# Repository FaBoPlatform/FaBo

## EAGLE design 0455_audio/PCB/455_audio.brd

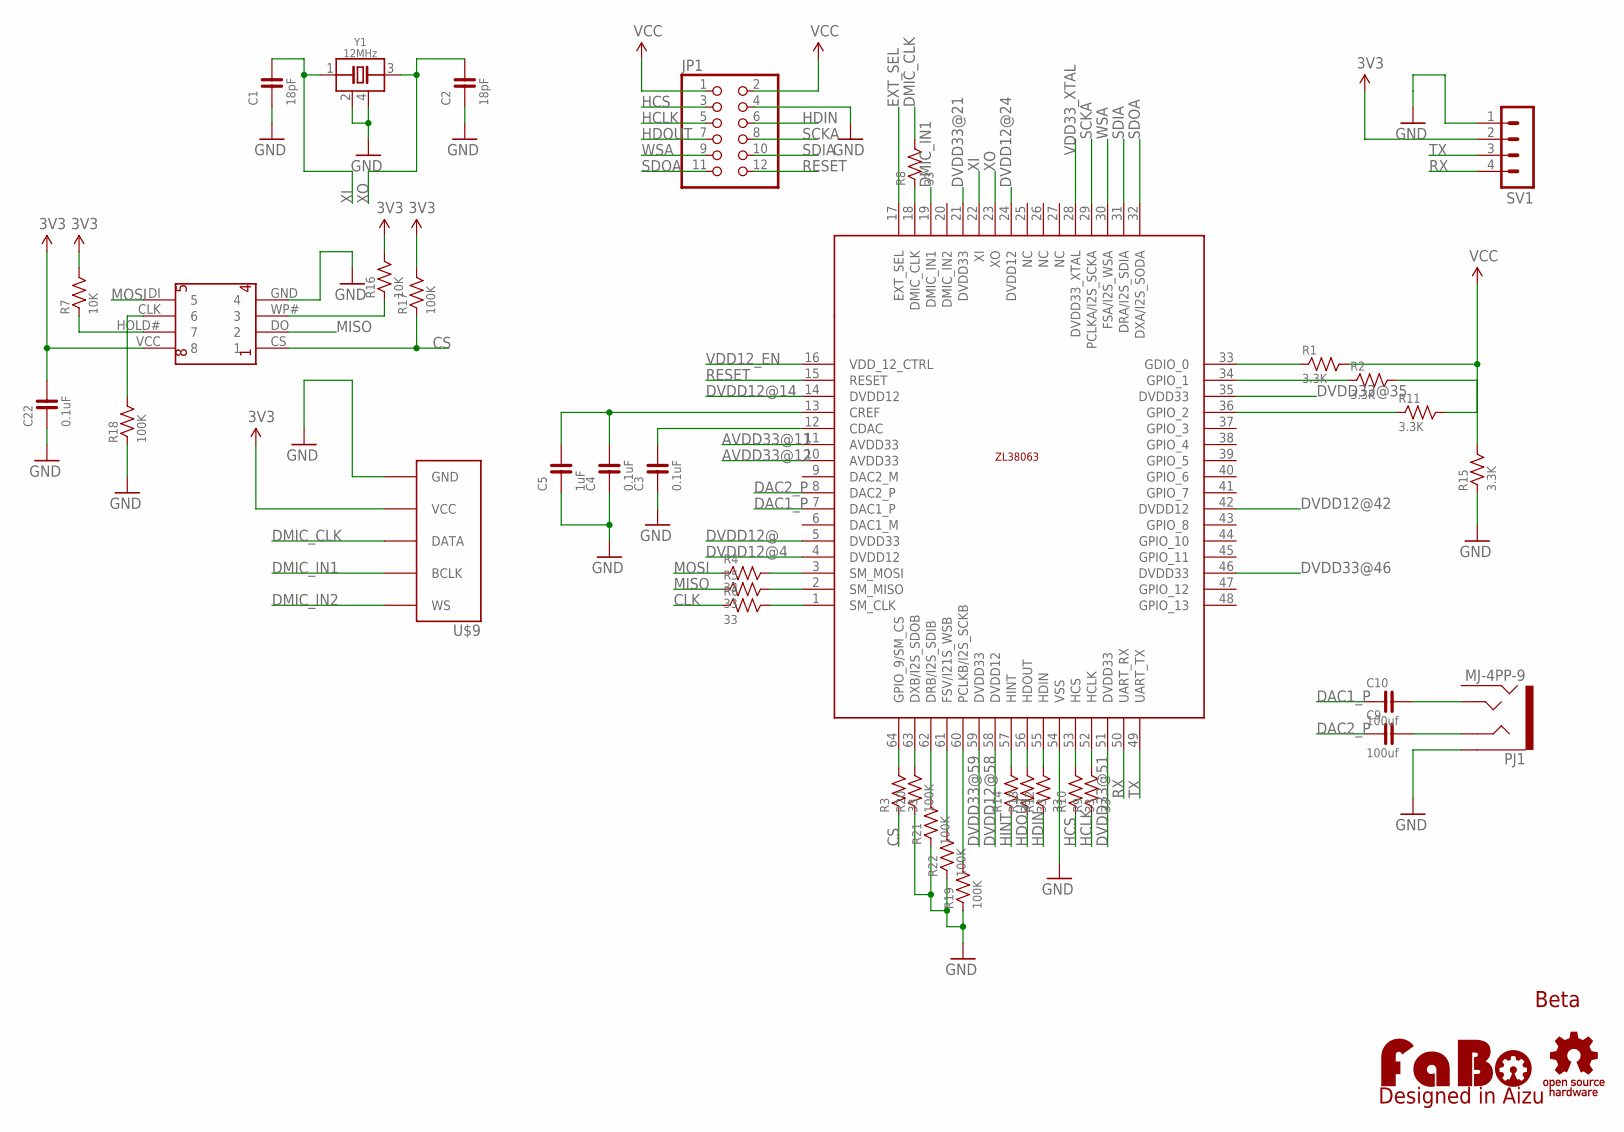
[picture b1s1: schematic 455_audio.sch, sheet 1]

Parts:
C1, C2: 18pF; 0603
C3, C4, C22: 0.1uF; 0603
C5: 1uF; 0603
C9, C10: 100uf; 0603
JP1: PINHD-2X6; 2X06
LOGO1: LOGO_FABO-M; LOGO_FABO_M
PJ1: MJ-4PP-9; PHONEJACK-MJ-4PP-9
R1, R2, R11, R15: 3.3K; 0603
R3, R4, R5, R6, R8, R9, R10, R12, R13, R14: 33; 0603
R7, R16: 10K; 0603
R17, R18, R19, R20, R21, R22: 100K; 0603
SV1: MA04-1
U$2: ZL38063
U$5: LOGO_OSHW-M_BOTTOM; LOGO_OSHW_M_BOTTOM
U$6: FLASH-MEMORY-2M(WINBOND)
U$9: FABO_BRICK_I2SLONG_BOTTOM; FABO_BRICK_I2S_S05B-PASK-2_LONG_BOTTOM
Y1: 12MHz; ECS-12MHZ

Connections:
3V3: C22.2, R7.2, R16.2, R17.2, SV1.2, U$6.VCC (8), U$9.VCC; also elsewhere on the board
AVDD33@11: U$2.11 (AVDD33)
AVDD33@12: U$2.10 (AVDD33)
CLK: R6.1, R18.2, U$6.CLK (6)
CS: R3.1, R17.1, U$6.CS (1)
DAC1_P: C10.1, U$2.7 (DAC1_P)
DAC2_P: C9.1, U$2.8 (DAC2_P)
DMIC_CLK: R8.2, U$9.DATA
DMIC_IN1: U$2.19 (DMIC_IN1), U$9.BCLK
DMIC_IN2: U$9.WS
DVDD12@: U$2.5 (DVDD33); also elsewhere on the board
DVDD12@4: U$2.4 (DVDD12); also elsewhere on the board
DVDD12@14: U$2.14 (DVDD12); also elsewhere on the board
DVDD12@24: U$2.24 (DVDD12); also elsewhere on the board
DVDD12@42: U$2.42 (DVDD12); also elsewhere on the board
DVDD12@58: U$2.58 (DVDD12); also elsewhere on the board
DVDD33@21: U$2.21 (DVDD33); also elsewhere on the board
DVDD33@35: U$2.35 (DVDD33); also elsewhere on the board
DVDD33@46: U$2.46 (DVDD33); also elsewhere on the board
DVDD33@51: U$2.51 (DVDD33); also elsewhere on the board
DVDD33@59: U$2.59 (DVDD33); also elsewhere on the board
EXT_SEL: U$2.17 (EXT_SEL); also elsewhere on the board
GND: C1.1, C2.1, C3.1, C4.1, C5.1, C22.1, JP1.4, PJ1.A, R15.1, R18.1, R19.1, R20.1, R21.1, R22.1, SV1.1, U$2.54 (VSS), U$6.GND (4), U$9.GND, Y1.2 (GND), Y1.4 (GND); also elsewhere on the board
HCLK: JP1.5, R9.1
HCS: JP1.3, R10.1
HDIN: JP1.6, R12.1
HDOUT: JP1.7, R13.1
HINT: R14.1
MISO: R5.1, U$6.DO (2)
MOSI: R4.1, U$6.DI (5)
unnamed: R1.1, U$2.33 (GDIO_0)
unnamed: R2.1, U$2.34 (GPIO_1)
unnamed: C3.2, U$2.12 (CDAC)
unnamed: C4.2, C5.2, U$2.13 (CREF)
unnamed: R3.2, U$2.64 (GPIO_9/SM_CS)
unnamed: R20.2, U$2.63 (DXB/I2S_SDOB)
unnamed: R11.1, U$2.36 (GPIO_2)
unnamed: R5.2, U$2.2 (SM_MISO)
unnamed: R6.2, U$2.1 (SM_CLK)
unnamed: C9.2, PJ1.C
unnamed: C10.2, PJ1.D
unnamed: R4.2, U$2.3 (SM_MOSI)
unnamed: R8.1, U$2.18 (DMIC_CLK)
unnamed: R14.2, U$2.57 (HINT)
unnamed: R13.2, U$2.56 (HDOUT)
unnamed: R12.2, U$2.55 (HDIN)
unnamed: R10.2, U$2.53 (HCS)
unnamed: R9.2, U$2.52 (HCLK)
unnamed: R11.2, R15.2
unnamed: R7.1, U$6.HOLD# (7)
unnamed: R16.1, U$6.WP# (3)
unnamed: R21.2, U$2.62 (DRB/I2S_SDIB)
unnamed: R22.2, U$2.61 (FSV/I21S_WSB)
unnamed: R19.2, U$2.60 (PCLKB/I2S_SCKB)
RESET: JP1.12, U$2.15 (RESET)
RX: SV1.4, U$2.50 (UART_RX)
SCKA: JP1.8, U$2.29 (PCLKA/I2S_SCKA)
SDIA: JP1.10, U$2.31 (DRA/I2S_SDIA)
SDOA: JP1.11, U$2.32 (DXA/I2S_SODA)
TX: SV1.3, U$2.49 (UART_TX)
VCC: JP1.1, JP1.2, R1.2, R2.2; also elsewhere on the board
VDD12_EN: U$2.16 (VDD_12_CTRL); also elsewhere on the board
VDD33_XTAL: U$2.28 (DVDD33_XTAL)
WSA: JP1.9, U$2.30 (FSA/I2S_WSA)
XI: C1.2, U$2.22 (XI), Y1.1 (IO)
XO: C2.2, U$2.23 (XO), Y1.3 (IO)

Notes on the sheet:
Beta

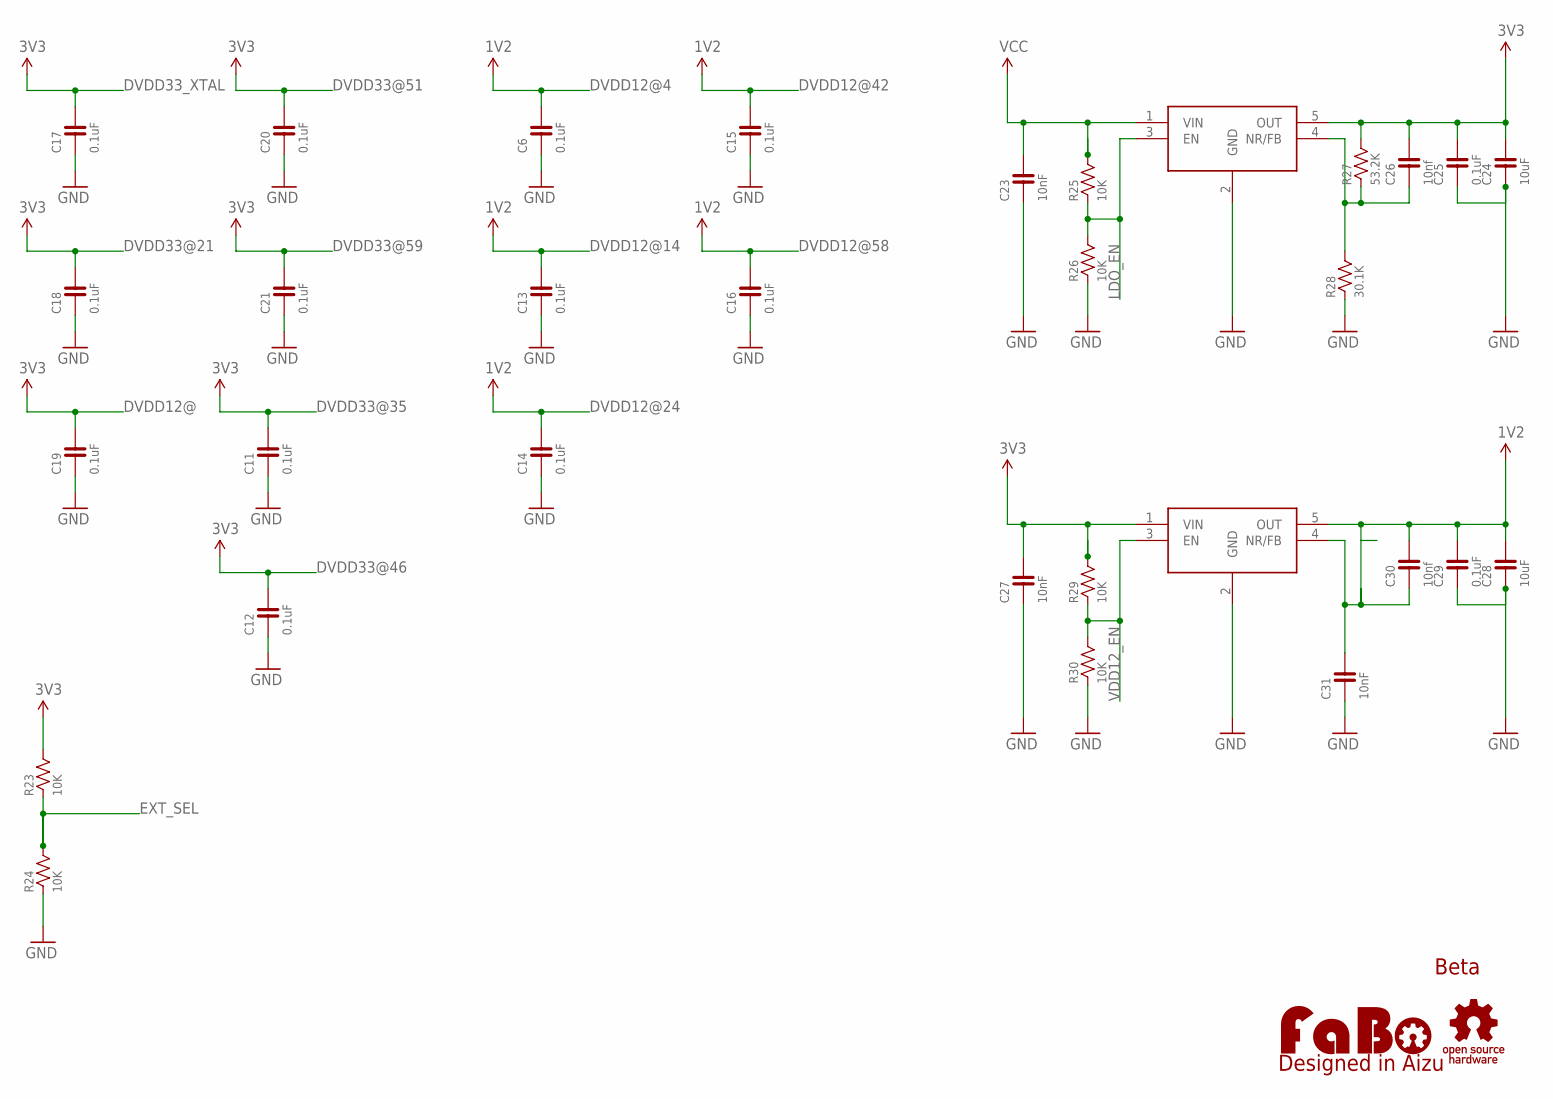
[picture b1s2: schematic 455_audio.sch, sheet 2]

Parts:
C6, C11, C12, C13, C14, C15, C16, C17, C18, C19, C20, C21, C25, C29: 0.1uF; 0603
C23, C27, C31: 10nF; 0603
C24, C28: 10uF; 0603
C26, C30: 10nf; 0603
R23, R24, R25, R26, R29, R30: 10K; 0603
R27: 53.2K; 0603
R28: 30.1K; 0603
U$7, U$8: TPS73601; SOT-23-5

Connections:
1V8: C28.2, C29.2, C30.2, U$8.5 (OUT)
3V3: C24.2, C25.2, C26.2, C27.2, R23.2, R27.2, R29.2, U$7.5 (OUT), U$8.1 (VIN); also elsewhere on the board
DVDD12@: C19.2; also elsewhere on the board
DVDD12@4: C6.2; also elsewhere on the board
DVDD12@14: C13.2; also elsewhere on the board
DVDD12@24: C14.2; also elsewhere on the board
DVDD12@42: C15.2; also elsewhere on the board
DVDD12@58: C16.2; also elsewhere on the board
DVDD33@21: C18.2; also elsewhere on the board
DVDD33@35: C11.2; also elsewhere on the board
DVDD33@46: C12.2; also elsewhere on the board
DVDD33@51: C20.2; also elsewhere on the board
DVDD33@59: C21.2; also elsewhere on the board
DVDD33_XTAL: C17.2
EXT_SEL: R23.1, R24.2; also elsewhere on the board
GND: C6.1, C11.1, C12.1, C13.1, C14.1, C15.1, C16.1, C17.1, C18.1, C19.1, C20.1, C21.1, C23.1, C24.1, C25.1, C27.1, C28.1, C29.1, C31.1, R24.1, R26.1, R28.1, R30.1, U$7.2 (GND), U$8.2 (GND); also elsewhere on the board
LDO_EN: R25.1, R26.2, U$7.3 (EN)
unnamed: C26.1, R27.1, R28.2, U$7.4 (NR/FB)
unnamed: C30.1, C31.2, U$8.4 (NR/FB)
VCC: C23.2, R25.2, U$7.1 (VIN); also elsewhere on the board
VDD12_EN: R29.1, R30.2, U$8.3 (EN); also elsewhere on the board

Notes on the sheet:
Beta

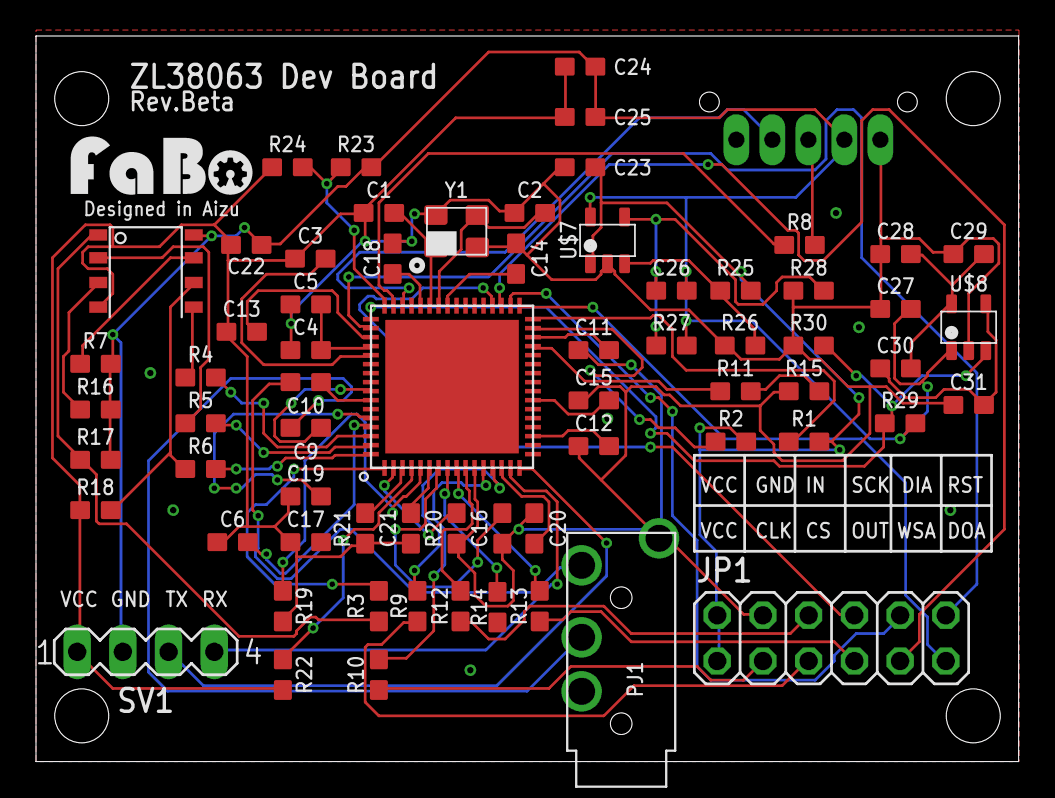
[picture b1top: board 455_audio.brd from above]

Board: 2 copper layers, 54.6 x 40.3 mm, 70 parts (0 on the bottom side), 65 nets.

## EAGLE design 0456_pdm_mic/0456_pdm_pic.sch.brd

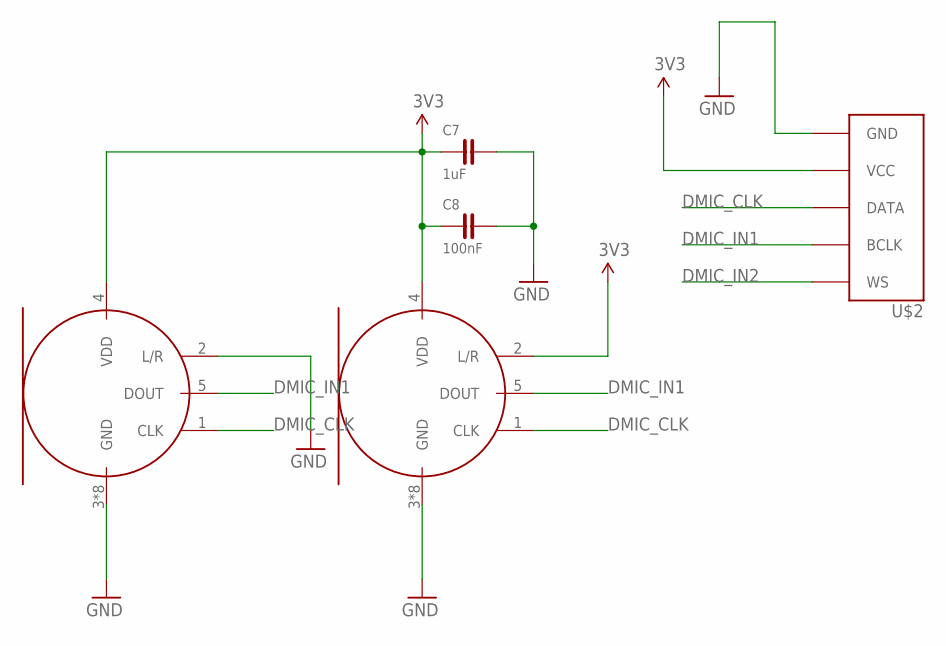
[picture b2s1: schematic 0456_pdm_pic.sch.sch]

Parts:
C7: 1uF; 0603
C8: 100nF; 0603
LEFT: PDM_MIC-INMP621; INMP621
RIGHT: PDM_MIC-INMP621; INMP621
U$2: FABO_BRICK_I2SLONG_BOTTOM; FABO_BRICK_I2S_S05B-PASK-2_LONG_BOTTOM

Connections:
3V3: C7.1, C8.1, LEFT.4 (VDD), RIGHT.2 (L/R), RIGHT.4 (VDD), U$2.VCC
DMIC_CLK: LEFT.1 (CLK), RIGHT.1 (CLK), U$2.DATA
DMIC_IN1: LEFT.5 (DOUT), RIGHT.5 (DOUT), U$2.BCLK
DMIC_IN2: U$2.WS
GND: C7.2, C8.2, LEFT.2 (L/R), LEFT.3 (GND), LEFT.6 (GND), LEFT.7 (GND), LEFT.8 (GND), LEFT.9 (GND), LEFT.10 (GND), LEFT.11 (GND), LEFT.12 (GND), RIGHT.3 (GND), RIGHT.6 (GND), RIGHT.7 (GND), RIGHT.8 (GND), RIGHT.9 (GND), RIGHT.10 (GND), RIGHT.11 (GND), RIGHT.12 (GND), U$2.GND

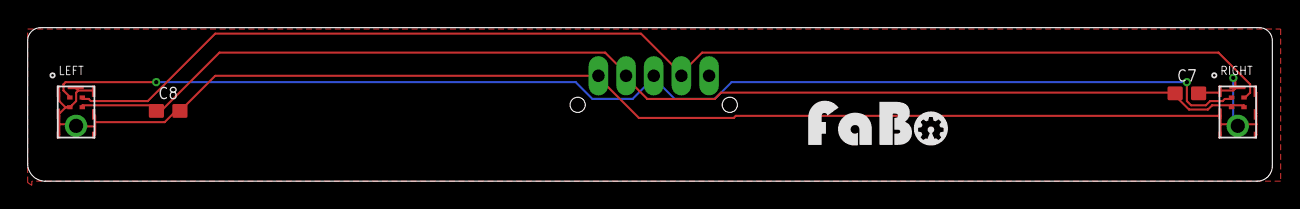
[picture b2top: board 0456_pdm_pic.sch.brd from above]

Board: 2 copper layers, 90.0 x 11.1 mm, 6 parts (0 on the bottom side), 4 nets.

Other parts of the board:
U$3: LOGO_FABO_MS

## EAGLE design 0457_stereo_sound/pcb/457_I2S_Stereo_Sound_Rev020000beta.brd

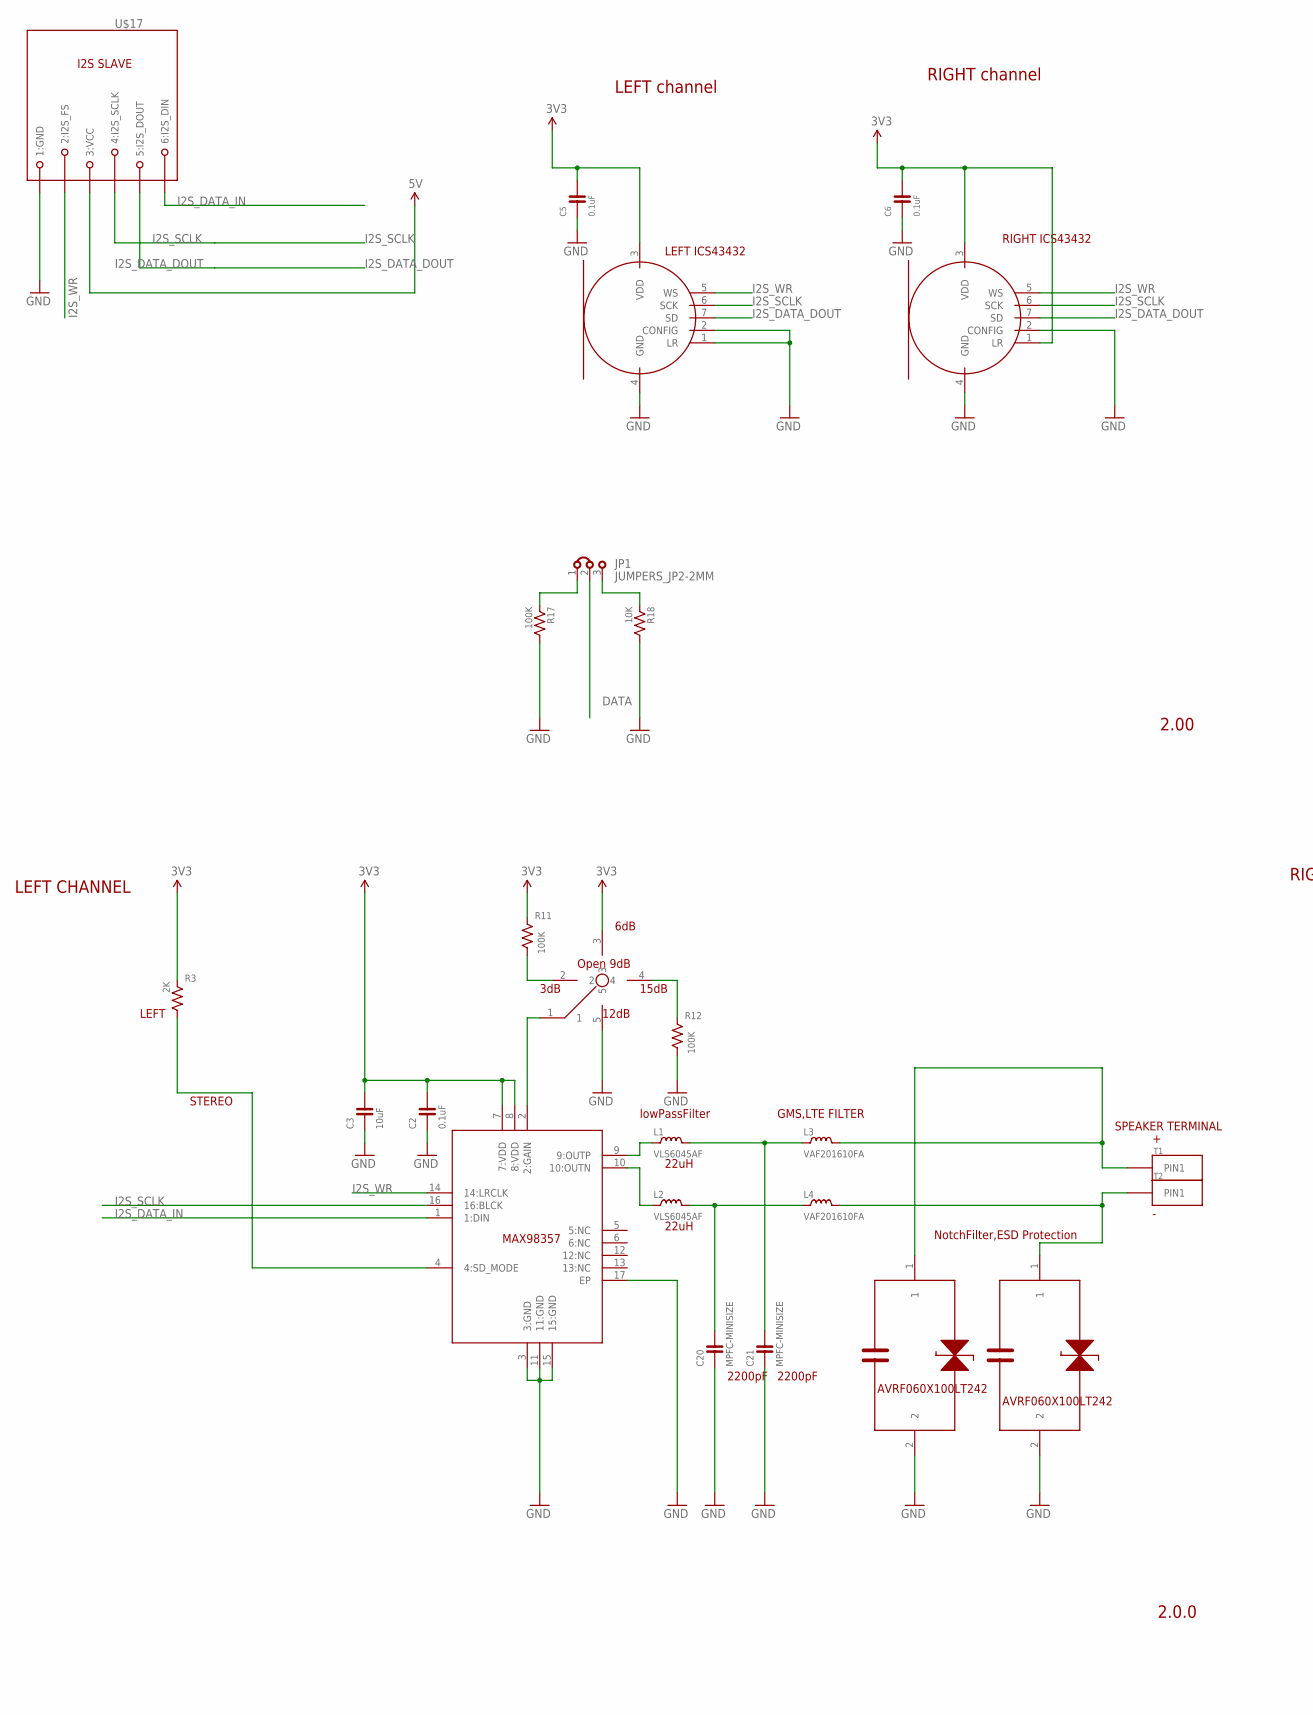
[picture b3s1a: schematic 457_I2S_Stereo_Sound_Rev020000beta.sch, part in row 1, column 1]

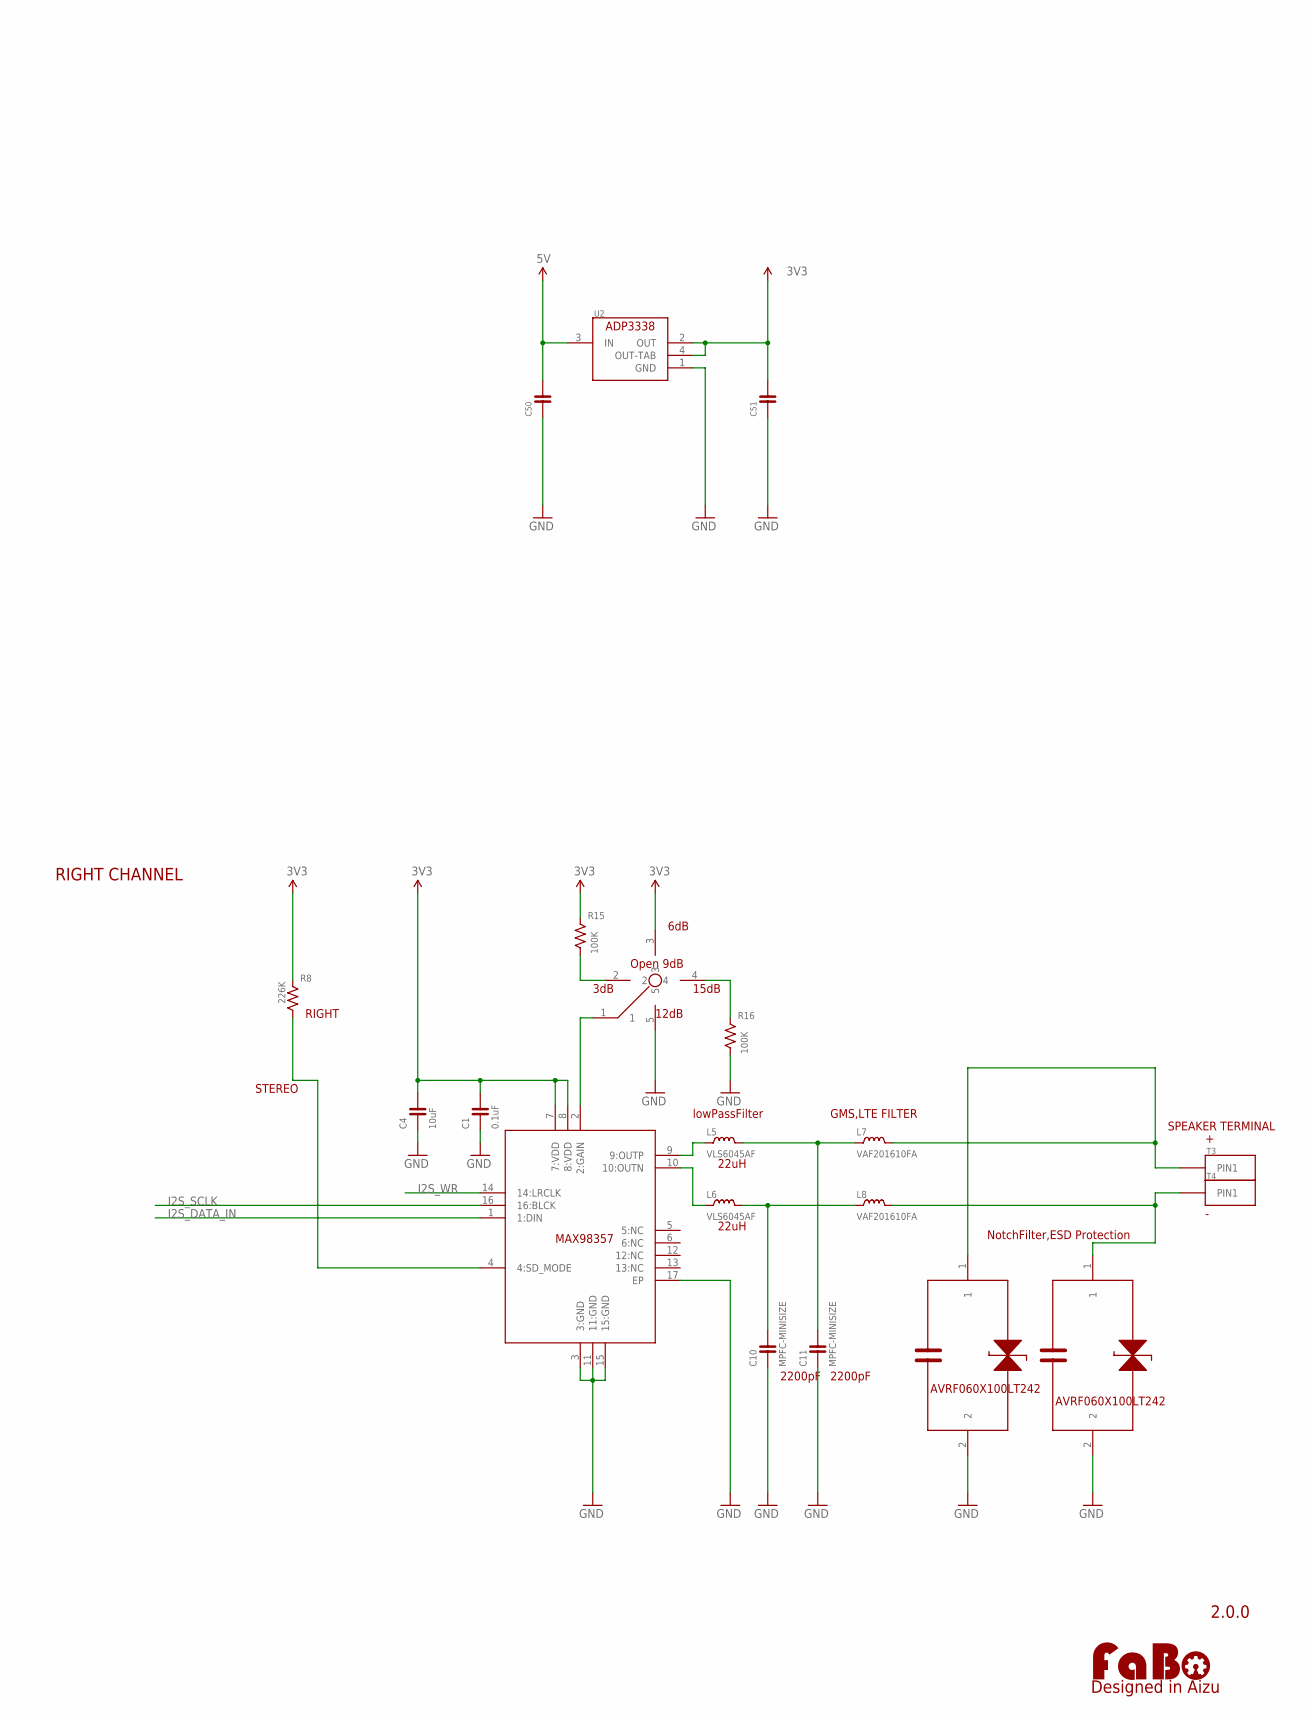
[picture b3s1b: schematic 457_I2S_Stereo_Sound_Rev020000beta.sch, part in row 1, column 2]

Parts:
C1, C2: 0.1uF; 0603
C3, C4: 10uF; 0603
C5, C6: 0.1uF; 0402
C10, C11, C20, C21: MPFC-MINISIZE; DIP-MPFC
C50, C51: CAPACITOR-POLYMAR-AUDIO; 4532
JP1: JUMPERS_JP2-2MM
L1, L2, L5, L6: VLS6045AF
L3, L4, L7, L8: VAF201610FA; VAF201610FA-1
LEFTAMP: MAX98357A,B; TQFN(16L3*3*0.75)
LOGO1: LOGO_FABO-M; LOGO_FABO_M
MIC_LEFT: TDK-ICS43432
MIC_RIGHT: TDK-ICS43432
R3: 2K; 0603
R8: 226K; 0603
R11, R12, R15, R16, R17: 100K; 0603
R18: 10K; 0603
RIGHTAMP: MAX98357A,B; TQFN(16L3*3*0.75)
T1, T2, T3, T4: TBL004-508
U2: ADP3338AKCZ; SOT-223-KC3
U$5, U$7, U$9, U$11: AVRF060X100LT242; AVRF0X0X100LT_0603
U$13, U$14: 2MMJUMPER_CROSS; PINHEAD2MM_CROSS
U$17: MODULAR-JACK-6P-RJ11_I2S_SLAVE; 7002-6PXC-X

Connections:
3DB: R11.2, U$13.2
3DB1: R15.2, U$14.2
3V3: C1.2, C2.2, C3.2, C4.2, C5.2, C6.2, C51.2, LEFTAMP.7 (7:VDD), LEFTAMP.8 (8:VDD), MIC_LEFT.3 (VDD), MIC_RIGHT.1 (LR), MIC_RIGHT.3 (VDD), R3.1, R8.1, R11.1, R15.1, RIGHTAMP.7 (7:VDD), RIGHTAMP.8 (8:VDD), U2.2 (OUT), U2.4 (OUT-TAB), U$13.3, U$14.3; also elsewhere on the board
5V: C50.2, U2.3 (IN), U$17.3 (3:VCC); also elsewhere on the board
15DB: R12.1, U$13.4
15DB1: R16.1, U$14.4
DATA: JP1.2
GAIN: LEFTAMP.2 (2:GAIN), U$13.1
GAIN1: RIGHTAMP.2 (2:GAIN), U$14.1
GND: C1.1, C2.1, C3.1, C4.1, C5.1, C6.1, C10.1, C11.1, C20.1, C21.1, C50.1, C51.1, LEFTAMP.3 (3:GND), LEFTAMP.11 (11:GND), LEFTAMP.15 (15:GND), LEFTAMP.17 (EP), MIC_LEFT.1 (LR), MIC_LEFT.2 (CONFIG), MIC_LEFT.4 (GND), MIC_RIGHT.2 (CONFIG), MIC_RIGHT.4 (GND), R12.2, R16.2, R17.2, R18.2, RIGHTAMP.3 (3:GND), RIGHTAMP.11 (11:GND), RIGHTAMP.15 (15:GND), RIGHTAMP.17 (EP), U2.1 (GND), U$5.2, U$7.2, U$9.2, U$11.2, U$13.5, U$14.5, U$17.1 (1:GND); also elsewhere on the board
I2S_DATA_DOUT: MIC_LEFT.7 (SD), MIC_RIGHT.7 (SD), U$17.5 (5:I2S_DOUT)
I2S_DATA_IN: LEFTAMP.1 (1:DIN), RIGHTAMP.1 (1:DIN), U$17.6 (6:I2S_DIN)
I2S_SCLK: LEFTAMP.16 (16:BLCK), MIC_LEFT.6 (SCK), MIC_RIGHT.6 (SCK), RIGHTAMP.16 (16:BLCK), U$17.4 (4:I2S_SCLK)
I2S_WR: LEFTAMP.14 (14:LRCLK), MIC_LEFT.5 (WS), MIC_RIGHT.5 (WS), RIGHTAMP.14 (14:LRCLK), U$17.2 (2:I2S_FS)
LEFTN: L4.2, T2.P$1, T2.P$2, U$11.1
LEFTP: L3.2, T1.P$1, T1.P$2, U$9.1
MS: LEFTAMP.4 (4:SD_MODE), R3.2
MS1: R8.2, RIGHTAMP.4 (4:SD_MODE)
unnamed: JP1.1, R17.1
unnamed: JP1.3, R18.1
OPTN2: C20.2, L2.2, L4.1
OUTN: L2.1, LEFTAMP.10 (10:OUTN)
OUTP: L1.1, LEFTAMP.9 (9:OUTP)
OUTP2: C21.2, L1.2, L3.1
OUTRN: L6.1, RIGHTAMP.10 (10:OUTN)
OUTRN2: C10.2, L6.2, L8.1
OUTRP: L5.1, RIGHTAMP.9 (9:OUTP)
OUTRP2: C11.2, L5.2, L7.1
RIGHTN: L8.2, T4.P$1, T4.P$2, U$7.1
RIGHTP: L7.2, T3.P$1, T3.P$2, U$5.1

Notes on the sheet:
2.0.0
22uH
AVRF060X100LT242
6dB
12dB
Open 9dB
LEFT
STEREO
lowPassFilter
NotchFilter,ESD Protection
GMS,LTE FILTER
SPEAKER TERMINAL
2200pF
3dB
15dB
RIGHT
2.00
LEFT ICS43432
RIGHT ICS43432
LEFT channel
RIGHT channel
LEFT CHANNEL
RIGHT CHANNEL

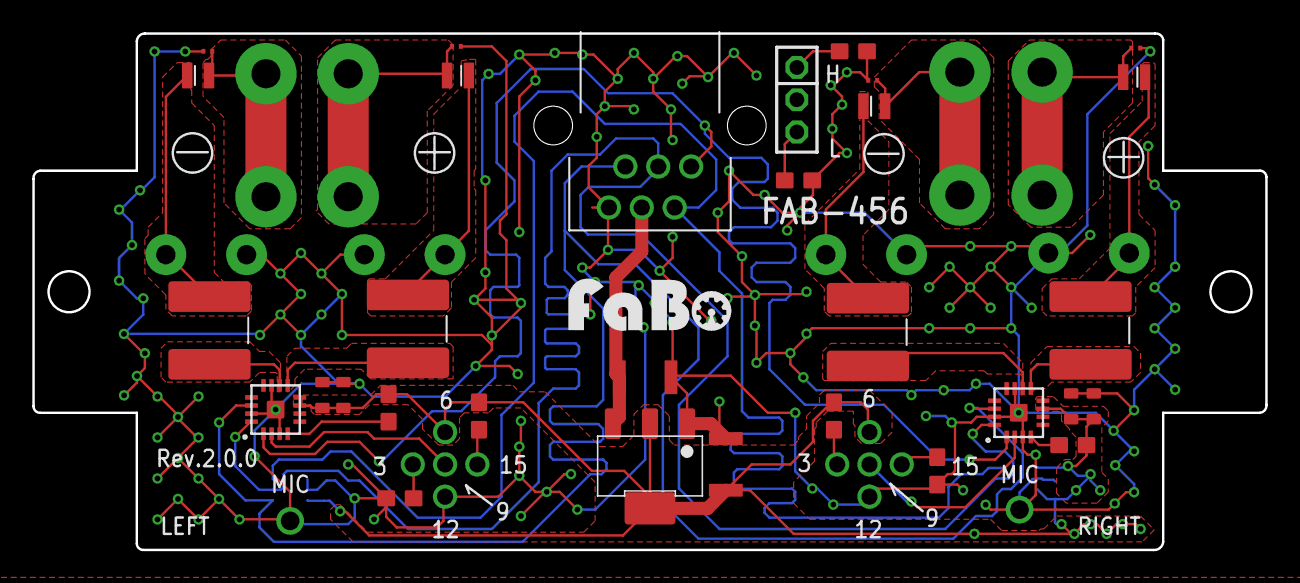
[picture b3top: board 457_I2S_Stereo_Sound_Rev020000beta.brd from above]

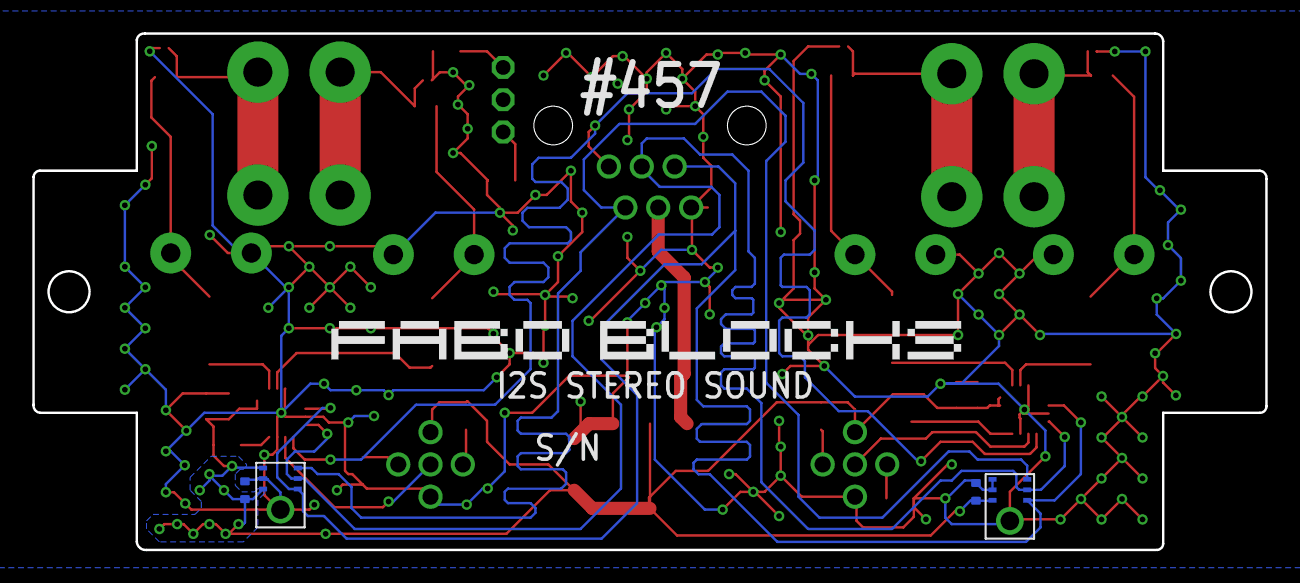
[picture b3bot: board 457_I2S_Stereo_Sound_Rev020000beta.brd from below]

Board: 2 copper layers, 76.4 x 32.0 mm, 48 parts (6 on the bottom side), 29 nets.

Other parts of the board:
C100, C101: AUDIO_CAPA; 3216
U$2, U$4: 4-1BLOCK

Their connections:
3V3: C101.2; also elsewhere on the board
5V: C100.2; also elsewhere on the board
GND: C100.1, C101.1; also elsewhere on the board

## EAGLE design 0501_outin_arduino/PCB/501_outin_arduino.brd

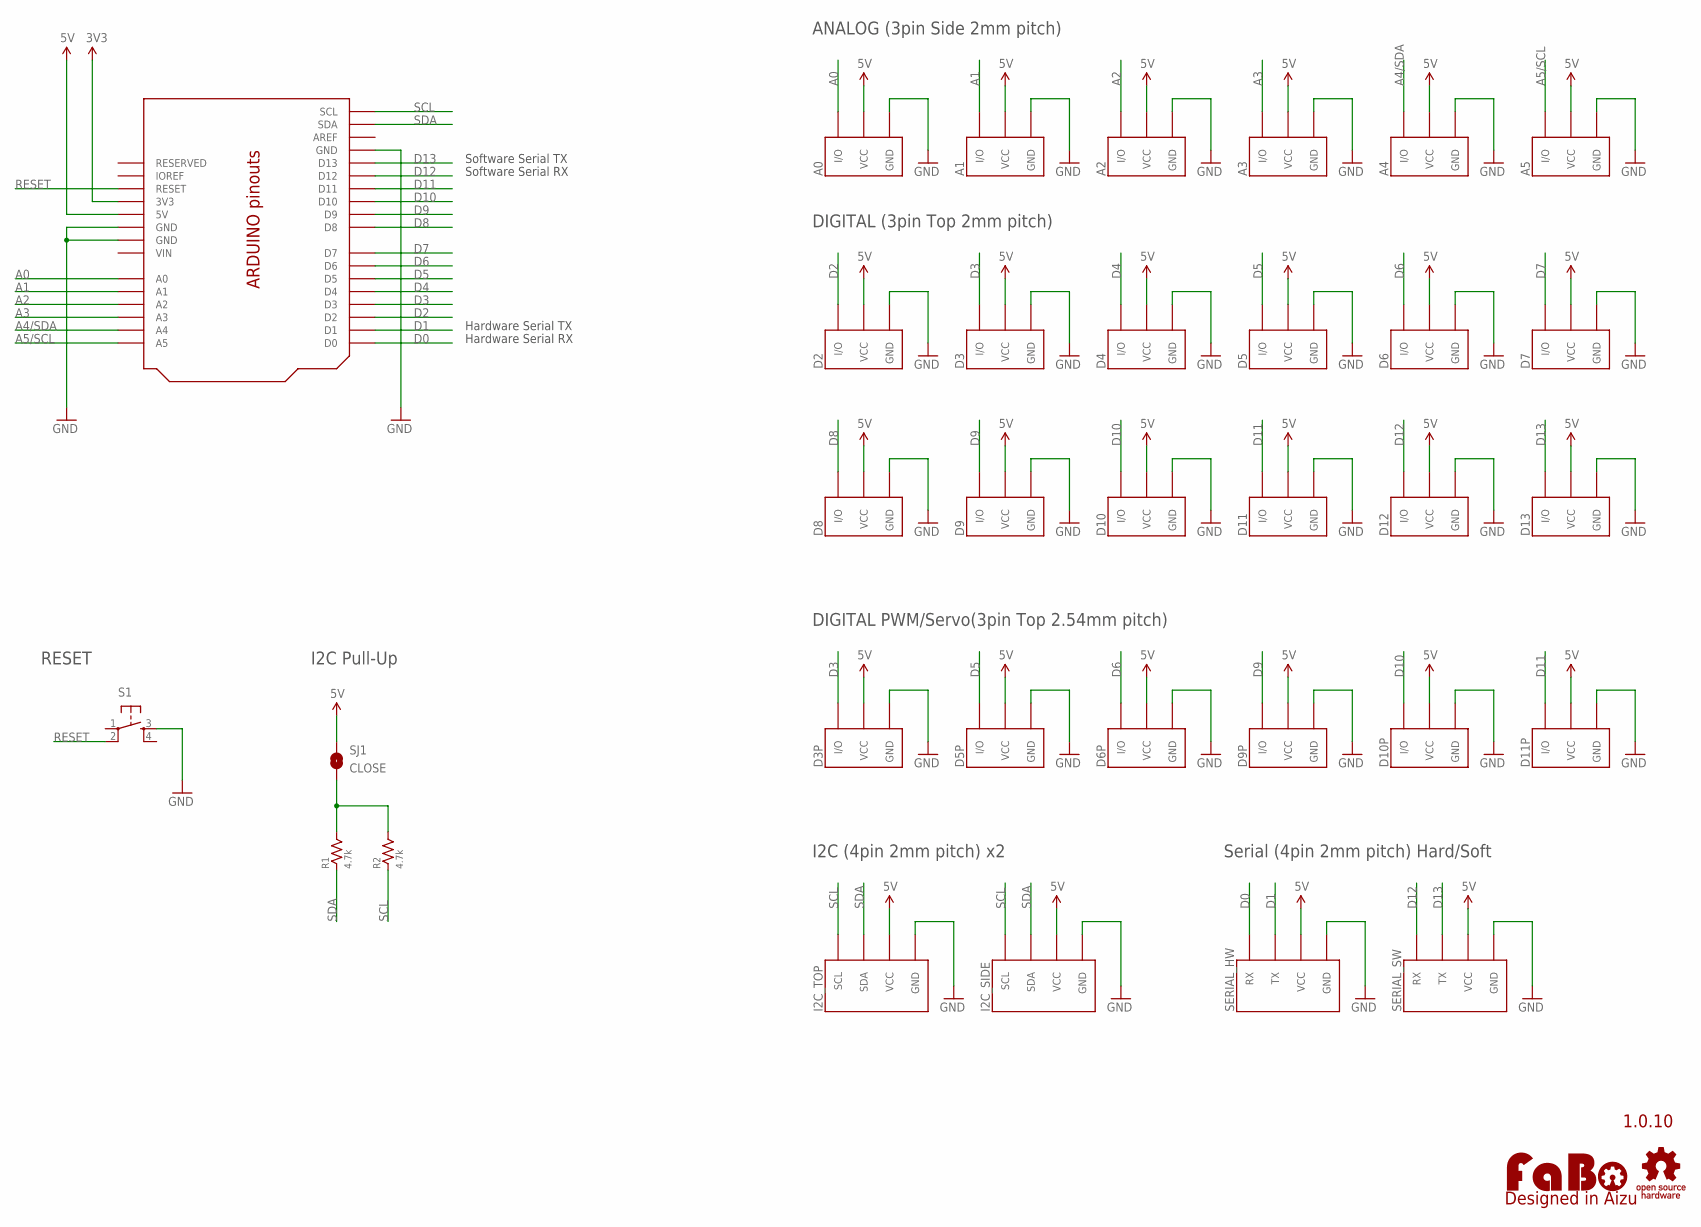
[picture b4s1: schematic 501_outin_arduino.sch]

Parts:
A0, A1, A2, A3, A4, A5: FABO_BRICK_3PIN-S03B-PASK-2_LONG; FABO_BRICK_3PIN_S03B-PASK-2_LONG
D2, D3, D4, D5, D6, D7, D8, D9, D10, D11, D12, D13: FABO_BRICK_3PIN-B03B-PASK-1; FABO_BRICK_3PIN_B03B-PASK-1
D3P, D5P, D6P, D9P, D10P, D11P: FABO_BRICK_3PIN-HEADER; FABO_BRICK_3PIN_HEADER
I2C_SIDE: FABO_BRICK_I2C-S04B-PASK-2_LONG; FABO_BRICK_I2C_S04B-PASK-2_LONG
I2C_TOP: FABO_BRICK_I2C-B04B-PASK-1; FABO_BRICK_I2C_B04B-PASK-1
LOGO1: LOGO_FABO-M_BOTTOM; LOGO_FABO_M_BOTTOM
R1, R2: 4.7k; 0603
S1: TACT-SWITCH-6MM; DTS_6_V
SERIAL_HW: FABO_BRICK_SERIAL-B04B-PASK-1; FABO_BRICK_SERIAL_B04B-PASK-1
SERIAL_SW: FABO_BRICK_SERIAL-S04B-PASK-2_LONG; FABO_BRICK_SERIAL_S04B-PASK-2_LONG
SJ1: CLOSE; SMD-JUMPER-2-CLOSE
U1: ARDUINO_UNO_R3_SHIELD-OUTIN; ARDUINO_SHIELD_OUTIN
U$13: LOGO_OSHW-T_M_BOTTOM; LOGO_OSHW_T_MS_BOTTOM

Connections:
3V3: U1.3V3
5V: A0.VCC, A1.VCC, A2.VCC, A3.VCC, A4.VCC, A5.VCC, D2.VCC, D3.VCC, D3P.VCC, D4.VCC, D5.VCC, D5P.VCC, D6.VCC, D6P.VCC, D7.VCC, D8.VCC, D9.VCC, D9P.VCC, D10.VCC, D10P.VCC, D11.VCC, D11P.VCC, D12.VCC, D13.VCC, I2C_SIDE.VCC, I2C_TOP.VCC, SERIAL_HW.VCC, SERIAL_SW.VCC, SJ1.1, U1.5V
A0: A0.I/O, U1.A0
A1: A1.I/O, U1.A1
A2: A2.I/O, U1.A2
A3: A3.I/O, U1.A3
A4/SDA: A4.I/O, U1.A4
A5/SCL: A5.I/O, U1.A5
D0: SERIAL_HW.RX, U1.D0
D1: SERIAL_HW.TX, U1.D1
D2: D2.I/O, U1.D2
D3: D3.I/O, D3P.I/O, U1.D3
D4: D4.I/O, U1.D4
D5: D5.I/O, D5P.I/O, U1.D5
D6: D6.I/O, D6P.I/O, U1.D6
D7: D7.I/O, U1.D7
D8: D8.I/O, U1.D8
D9: D9.I/O, D9P.I/O, U1.D9
D10: D10.I/O, D10P.I/O, U1.D10
D11: D11.I/O, D11P.I/O, U1.D11
D12: D12.I/O, SERIAL_SW.RX, U1.D12
D13: D13.I/O, SERIAL_SW.TX, U1.D13
GND: A0.GND, A1.GND, A2.GND, A3.GND, A4.GND, A5.GND, D2.GND, D3.GND, D3P.GND, D4.GND, D5.GND, D5P.GND, D6.GND, D6P.GND, D7.GND, D8.GND, D9.GND, D9P.GND, D10.GND, D10P.GND, D11.GND, D11P.GND, D12.GND, D13.GND, I2C_SIDE.GND, I2C_TOP.GND, S1.3, SERIAL_HW.GND, SERIAL_SW.GND, U1.GND1 (GND), U1.GND2 (GND), U1.GND3 (GND)
unnamed: R1.2, R2.2, SJ1.2
RESET: S1.2, U1.RESET
SCL: I2C_SIDE.SCL, I2C_TOP.SCL, R2.1, U1.SCL
SDA: I2C_SIDE.SDA, I2C_TOP.SDA, R1.1, U1.SDA
VIN: U1.VIN

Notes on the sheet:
1.0.10
DIGITAL (3pin Top 2mm pitch)
ANALOG (3pin Side 2mm pitch)
DIGITAL PWM/Servo(3pin Top 2.54mm pitch)
I2C (4pin 2mm pitch) x2
Software Serial RX
Software Serial TX
Serial (4pin 2mm pitch) Hard/Soft
Hardware Serial TX
Hardware Serial RX
I2C Pull-Up
RESET

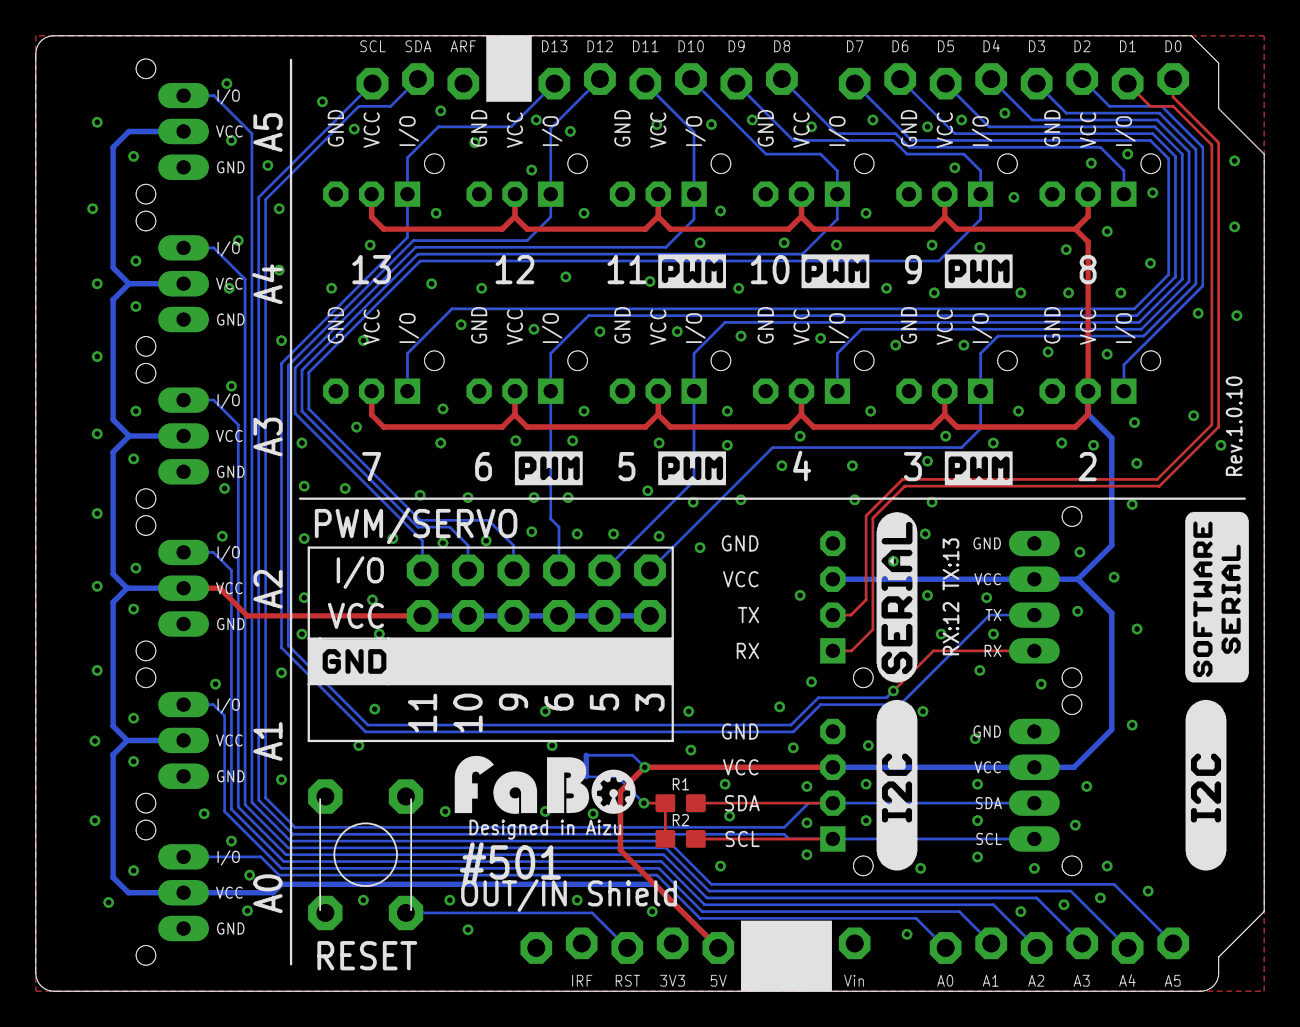
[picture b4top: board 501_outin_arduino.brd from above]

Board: 2 copper layers, 68.6 x 53.3 mm, 47 parts (1 on the bottom side), 26 nets.

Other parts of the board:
U$2: LOGO_SILK_SERIAL2
U$3: LOGO_SILK_SERIAL
U$4, U$5, U$6, U$7, U$8, U$9: LOGO_SILK_PWM
U$10: LOGO_FABO_M
U$11, U$12: LOGO_SILK_I2C
U$19: LOGO_SILK_GND

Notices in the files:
parts and their libraries:
FaBo-Capacitor: Released under the Creative Commons Attribution-ShareAlike 4.0 License
https://creativecommons.org/licenses/by-sa/4.0
FaBo-etc: Released under the Creative Commons
